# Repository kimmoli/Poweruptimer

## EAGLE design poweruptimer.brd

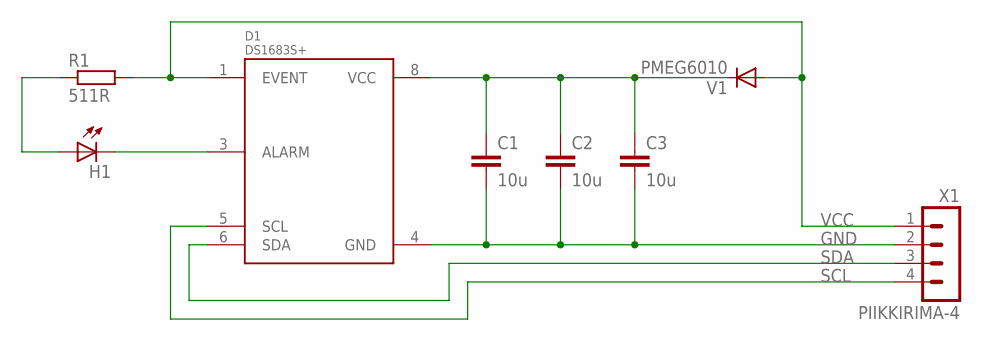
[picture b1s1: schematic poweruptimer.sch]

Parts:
C1, C2, C3: 10u; C0805
D1: DS1683S+; SOIC8-N_MC
H1: LEDCHIP-LED0603; CHIP-LED0603
R1: 511R; R0603
V1: PMEG6010; SOD323-R
X1: PIIKKIRIMA-4

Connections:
GND: C1.2, C2.2, C3.2, D1.4 (GND), X1.2
unnamed: C1.1, C2.1, C3.1, D1.8 (VCC), V1.C
unnamed: D1.3 (ALARM), H1.C
unnamed: H1.A, R1.1
SCL: D1.5 (SCL), X1.4
SDA: D1.6 (SDA), X1.3
VCC: D1.1 (EVENT), R1.2, V1.A, X1.1

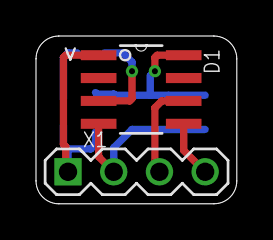
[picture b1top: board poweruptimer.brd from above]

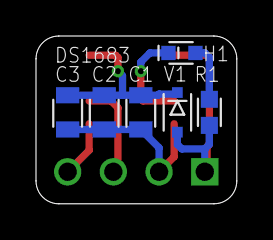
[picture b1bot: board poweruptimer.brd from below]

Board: 2 copper layers, 11.2 x 9.3 mm, 8 parts (6 on the bottom side), 7 nets.
